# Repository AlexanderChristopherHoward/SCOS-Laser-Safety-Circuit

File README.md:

# SCOS-Laser-Safety-Circuit
PCB board schematic and layout for safety circuit KiCAD

This is validation that I am able to push changes to GitHub

     _______
    /       \
    |  0-0  |
    \       /

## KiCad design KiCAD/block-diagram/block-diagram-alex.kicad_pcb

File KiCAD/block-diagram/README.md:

# SCOS Laser Safety PCB

## Rev 1 ECOs

* Reconnect VCC to 555 on schematic (<em>inconsistent with PCB!</em>)
* need input pull-ups on OVERRIDE, INTERLOCK, KEY_SW
  <br>on prototype, use 470 ohms on pins 1,5,6 of J1
  <br>(or fix on main board so logic driven)
  <br><em>The LEDs complicate this, perhaps LEDs should go to +5V instead?
* MOSFETs Q3, Q4 pinout is wrong :( :(
  <br> solder upside-down on prototype

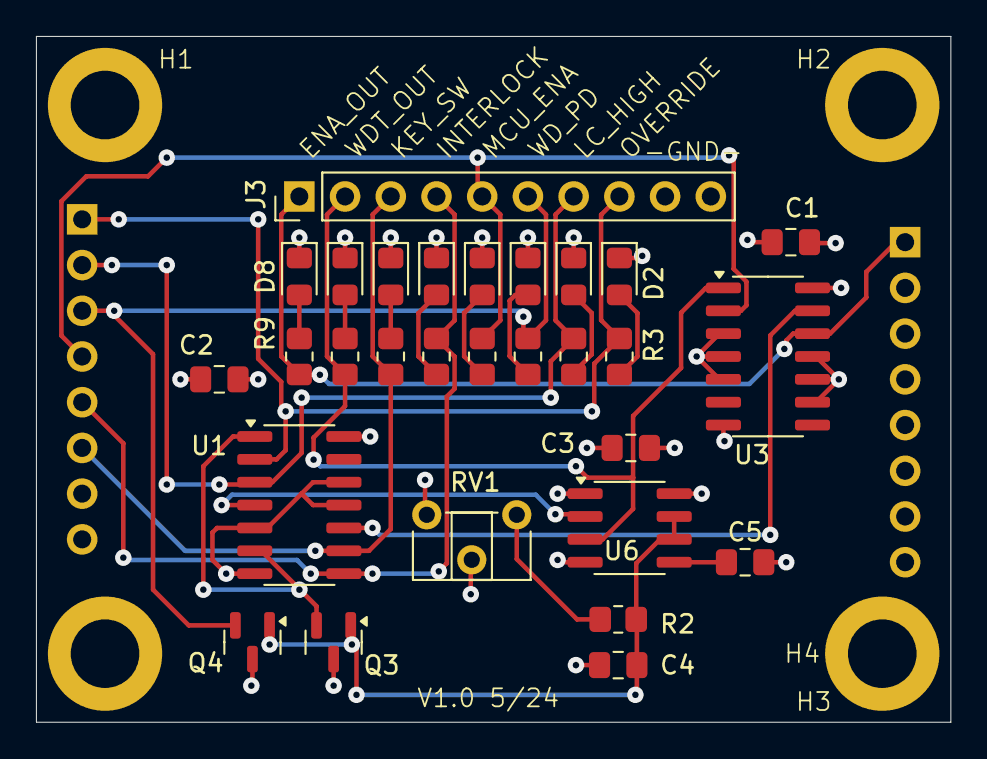
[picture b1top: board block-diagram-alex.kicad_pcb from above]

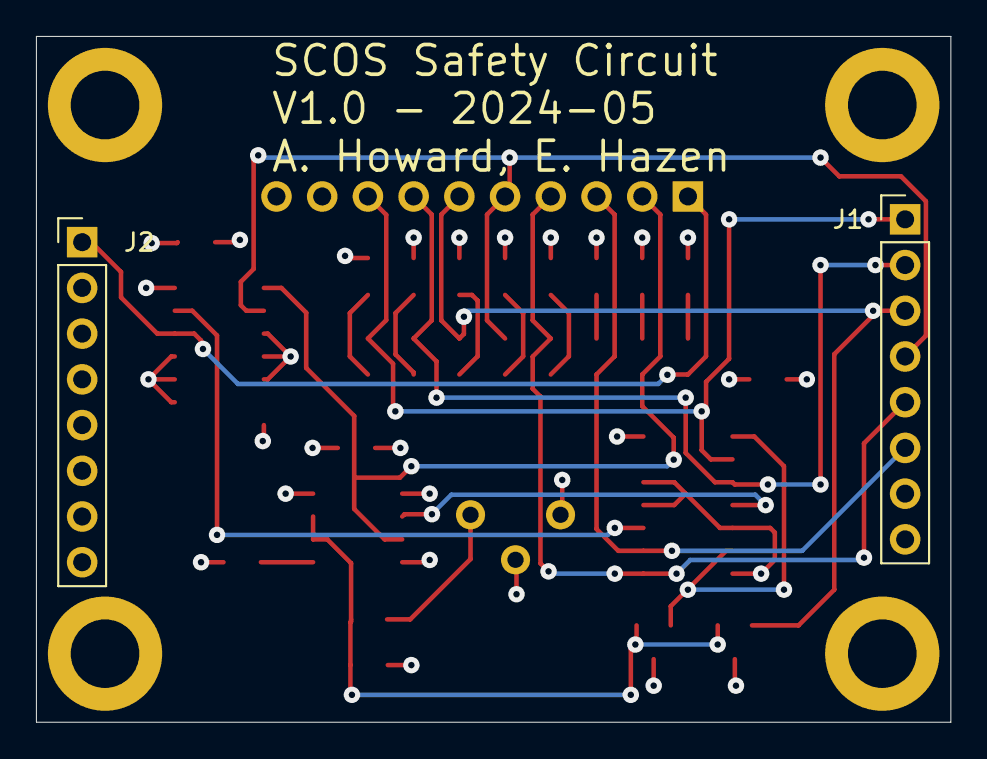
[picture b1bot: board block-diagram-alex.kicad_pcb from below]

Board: 4 copper layers, 50.8 x 38.1 mm, 35 parts (2 on the bottom side), 24 nets.

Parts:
C1, C2, C3, C4, C5: C_Small; C_0805_2012Metric_Pad1.18x1.45mm_HandSolder
D1, D2, D3, D4, D5, D6, D7, D8: LED; LED_0805_2012Metric_Pad1.15x1.40mm_HandSolder
H1, H2, H3, H4: MountingHole_Pad; hole_250_150
J1, J2: Conn_01x08; PinHeader_1x08_P2.54mm_Vertical
J3: Conn_01x10; PinHeader_1x10_P2.54mm_Vertical
Q3, Q4: NMOS; SOT-23
R1, R3, R4, R5, R6, R7, R8, R9: 470; R_0805_2012Metric_Pad1.20x1.40mm_HandSolder
R2: R_US; R_0805_2012Metric_Pad1.20x1.40mm_HandSolder
RV1: R_Potentiometer_US; Potentiometer_ACP_CA6-H2,5_Horizontal
U1: 74LS02; SOIC-14_3.9x8.7mm_P1.27mm
U3: 74LS11; SOIC-14_3.9x8.7mm_P1.27mm
U6: LMC555xM; SOIC-8_3.9x4.9mm_P1.27mm

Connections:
+5V: C1.1, C2.1, C3.1, J2.4, J2.5, RV1.2, RV1.3, U1.14 (VCC), U3.14 (VCC), U6.4 (R), U6.8 (VCC)
/INTERLOCK: J1.5, J3.4, R6.1, U1.8
/KEY_SW: J1.6, J3.3, R7.1, U1.9
/LASER_ENA: J2.1, J3.1, R9.1, U3.12
/LC_HIGH: J1.2, J3.7, R1.1, U1.3
/MCU_ENA: J1.4, J3.5, R5.1, U3.2
/OVERRIDE: J1.1, J3.8, R3.1, U1.2
/WDT_OUT: J3.2, R8.1, U3.1, U6.3 (Q)
/WD_PHOTODIODE: J1.3, J3.6, Q4.2 (G), R4.1
GND: C1.2, C2.2, C3.2, C4.2, C5.2, D1.1 (K), D2.1 (K), D3.1 (K), D4.1 (K), D5.1 (K), D6.1 (K), D7.1 (K), D8.1 (K), H1.1, H2.1, H3.1, H4.1, J2.6, J2.7, J2.8, J3.9, J3.10, Q3.3 (S), Q4.3 (S), U1.5, U1.7 (GND), U1.11, U1.12, U3.3, U3.4, U3.5, U3.7 (GND), U3.9, U3.10, U3.11, U6.1 (GND)
unnamed: D1.2 (A), R1.2
unnamed: D2.2 (A), R3.2
unnamed: D3.2 (A), R4.2
unnamed: D4.2 (A), R5.2
unnamed: D5.2 (A), R6.2
unnamed: D6.2 (A), R7.2
unnamed: D7.2 (A), R8.2
unnamed: D8.2 (A), R9.2
unnamed: C4.1, Q3.1 (D), Q4.1 (D), R2.2, U6.6 (THR), U6.7 (DIS)
unnamed: Q3.2 (G), U1.1, U1.6
unnamed: R2.1, RV1.1
unnamed: U1.10, U3.13
unnamed: C5.1, U6.5 (CV)
unnamed: U1.4, U6.2 (TR)

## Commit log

2024-04-02 KiCAD Schematic
    Added the KiCAD schematic for the safety circuit
2024-04-04 Eric's rendition for discussion
2024-04-17 Footprint Notes
    Notes on my decisions with footprints to go over with before moving forward, subject to change.
2024-04-17 add lck
2024-04-17 Add board-to-board connectors
2024-04-18 Updates With Footprint Assignment
    Adding MOSFET footprints, fixed note file name, fixed note file type from .txt to .md, still reading through documents to try to figure out how to put multiple gates on the same footprint.
2024-04-18 Attempt at layout
    I added components to the board and tried to get rid of the "rats nest". Still no luck with KiCAD documentation on how to assign multiple components to the same footprint. Mostly just proving to myse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
2024-04-19 trying to fix issues
    Issues with merging are preventing me to pull origin
2024-04-19 Schematic Updates
    Added 8 pin connectors. Connected power and ground to logic chips. Added capacitor and ground to the +5V for ICs. For unused logic gates, inputs tied to ground. No footprint assigned to 8 pin connect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
2024-04-19 PCB layout updates
    I updated the PCB with the components added to the schematic. I dimensioned a rectangle around the board that is 2x1.5 in and placed the 8 pin connecters with respect to the corners of the rectangle.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
2024-04-22 add mounting hole library/footprint
2024-04-22 tentative placement, add test points and LEDs
2024-04-22 add LEDs and test connector, update placement
2024-04-29 tweak placement
2024-04-29 fix some connectors
2024-05-01 demo some routing
2024-05-05 Potentiometer
    I added the potentiometer to modulate the watchdog time constant.
2024-05-06 Fix potentiometer
    Corrected wiring for potentiometer
2024-05-06 Rotate Pot
    Rotated potentiometer so pin 3 is on the left
2024-05-06 Fix pot in schematic
    rotated the potentiometer in the schematic to be the correct orientation so that it has the correct connections
2024-05-08 Added some ground vias
    Starting to work on routing
2024-05-09 Grounded, open pin of the 555
    There was a pin of the 555 that was connected to nothing, I connected it to ground, not sure if this is correct, but I believe generally that's what we are doing for unconnected pins, not sure if tha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
2024-05-09 Routing First Attempt
    I believe I performed the routing for the board. Note: we should verify which unused pins should be grounded.
2024-05-09 Added Via
    Fixed weird bug where there was a via that disappeared.
2024-05-09 Ran DRC
    There were only warnings no errors. One useless via was placed, I got rid of it. All other errors referred to the Silkscreen overlapping or being cut off by a component/via. I believe this just refer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
2024-05-09 Start filling symbol attributes; move J2 a bit
2024-05-10 Finishing Touches before adding Part and Cfg Nums
    * Fix silkscreen text overlaps
    * Move J2 up or down .05" and fix routing
    * Disconnect 555 pin 5 from GND and add a 10uF capacitor
    * Change U1, U3 from 74LS--- to 74HC---
2024-05-10 Capacitor CatNo and CfgNo
    Added part and cfg numbers for remaining capacitors, all are 10 nf.
2024-05-13 Bypass Capacitor changes and Value Update
    Changed all bypass capacitors to 0.1 uF and changed the value term to reflect capacitance.
2024-05-13 Logic Gate CatNo and MfgNo
    Added part and manufacturer numbers for the logic gates.
2024-05-13 Resistor part numbers for LED resistors
    Added part and manufacturer numbers for the resistors connected to the LED
2024-05-13 LED part number
    Added part and manufacturer numbers for the LEDs
2024-05-14 Part Nums for R and C of timer
    Added part numbers and values for the resistor and capacitor that control the circuit time constant. Still working on the potentiometer.
2024-05-14 Added Pot Value
    Labeled potentiometer with 50k, yet to add part and manufacturer numbers.
2024-05-14 Fixing Pink Labels
    Pink labels with part number have been moved to not cover important circuit elements
2024-05-14 Added Potentiometer Part number
    Added part number and manufacturer number for the potentiometer.
2024-05-14 Added Connector Part Numbers
    Part and manufacturer number for connectors.
2024-05-14 Removed J3 part number
    Removed the CatNo and MfgNo for J3
2024-05-14 Set connector J3 to do not populate
2024-05-21 Rev 1.0 as built
2024-06-10 Fix missing 5V on schematic, update README
